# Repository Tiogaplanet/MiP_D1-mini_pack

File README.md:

# MiP Power Up: D1 mini
A [D1 mini](https://wiki.wemos.cc/products:d1:d1_mini) adapter board for [WowWee Labs'](https://github.com/WowWeeLabs/) [MiP](https://wowwee.com/mip) robot.  Similar to the [MiP ProMini Pack](https://github.com/adamgreen/MiP_ProMini-Pack), this board adapts the D1 mini and compatible boards to MiP.  Install the D1 mini in a pair of pin headers and you'll be programming MiP to connect to the Internet in no time.

## Acknowledgment
* As always, a big "thank you" goes out to [adamgreen](https://github.com/adamgreen/).  Without his help I'd still be wondering why my MiP won't talk to an Arduino.  Now, it's talking to the Internet!
* I'd also like to thank [Casey Kuhns](https://github.com/caseykuhns) who while at [SparkFun](https://github.com/sparkfun) developed the original [ProMini Pack](https://github.com/sparkfun/mip_promini-pack) and the [ProtoPack](https://github.com/sparkfun/mip_proto-pack) which provided the foundation for this project.

## OSH Park renderings

## Installation
Please see the [wiki](https://github.com/Tiogaplanet/MPU_D1_mini/wiki) for up-to-date installation instructions.

## Disclaimer
I am a hobbyiest sharing this designed-at-home board with fans of robotics, MiP and the ESP8266 wifi chip.  While I strive to make this board as useful and "right" as it can be, in no way shall I be responsible for any damage that may occur to your MiP or D1 mini either incidently or directly through the use of this board.  You use this board at your own risk.

If you are experienced in robotics or circuit design and spot something that can or should be improved, please review [CONTRIBUTING.md](https://github.com/Tiogaplanet/MPU_D1_mini/blob/master/CONTRIBUTING.md) and submit a pull request.

## License
Shield: [![CC BY-SA 4.0][cc-by-sa-shield]][cc-by-sa]

This work is licensed under a
[Creative Commons Attribution-ShareAlike 4.0 International License][cc-by-sa].

[![CC BY-SA 4.0][cc-by-sa-image]][cc-by-sa]

[cc-by-sa]: http://creativecommons.org/licenses/by-sa/4.0/
[cc-by-sa-image]: https://licensebuttons.net/l/by-sa/4.0/88x31.png
[cc-by-sa-shield]: https://img.shields.io/badge/License-CC%20BY--SA%204.0-lightgrey.svg

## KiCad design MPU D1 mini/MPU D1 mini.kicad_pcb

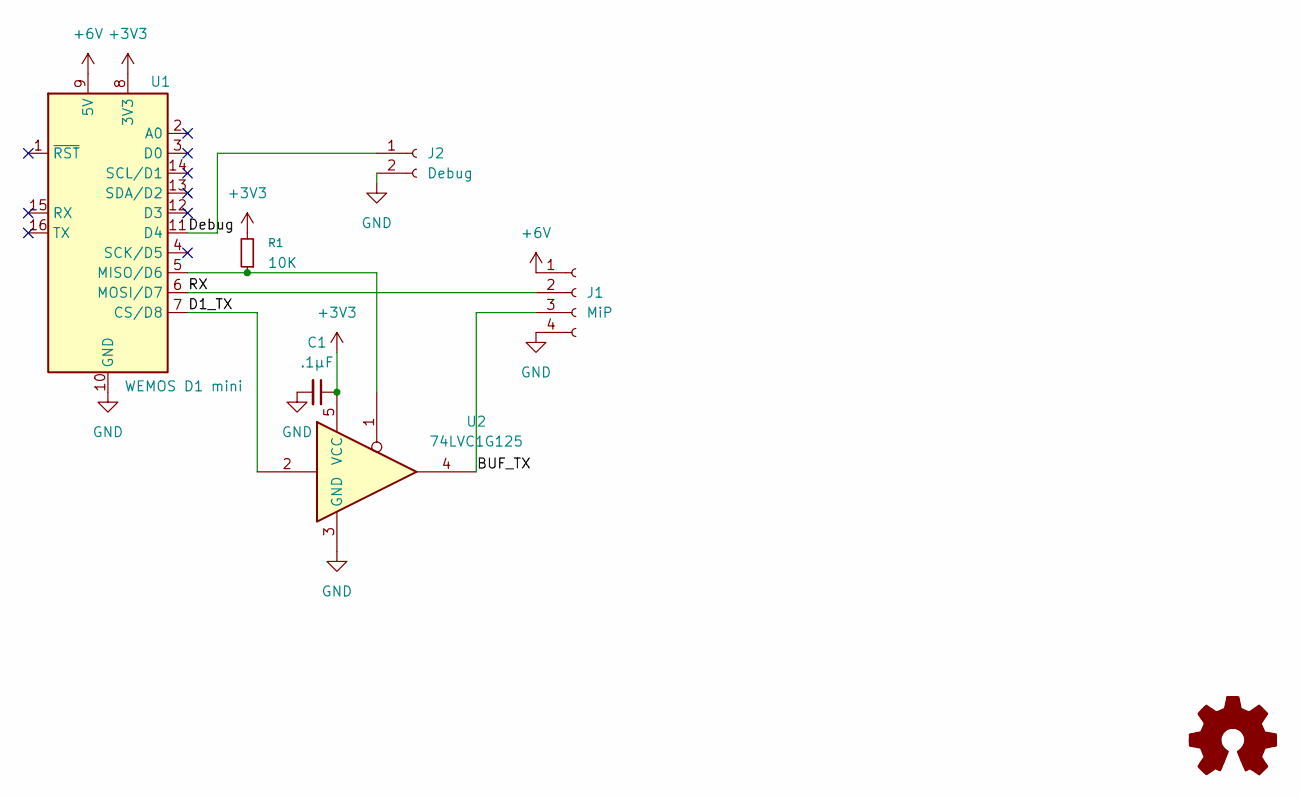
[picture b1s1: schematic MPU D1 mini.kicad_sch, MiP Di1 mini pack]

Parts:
C1: .1μF; C_0805_2012Metric_Pad1.18x1.45mm_HandSolder
J1: MiP; JST_ZH_B4B-ZR_1x04_P1.50mm_Vertical
J2: Debug; PinSocket_1x02_P2.54mm_Horizontal
R1: 10K; R_0805_2012Metric_Pad1.20x1.40mm_HandSolder
U1: WEMOS D1 mini; WEMOS_D1_mini_light
U2: 74LVC1G125; SOT-23-5_HandSoldering

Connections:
+3V3: C1.1, R1.2, U1.8 (3V3), U2.5 (VCC)
+6V: J1.1, U1.9 (5V)
/BUF_TX: J1.3, U2.4
/D1_TX: U1.7 (CS/D8), U2.2
/Debug: J2.1, U1.11 (D4)
/RX: J1.2, U1.6 (MOSI/D7)
GND: C1.2, J1.4, J2.2, U1.10 (GND), U2.3 (GND)
unnamed: R1.1, U1.5 (MISO/D6), U2.1

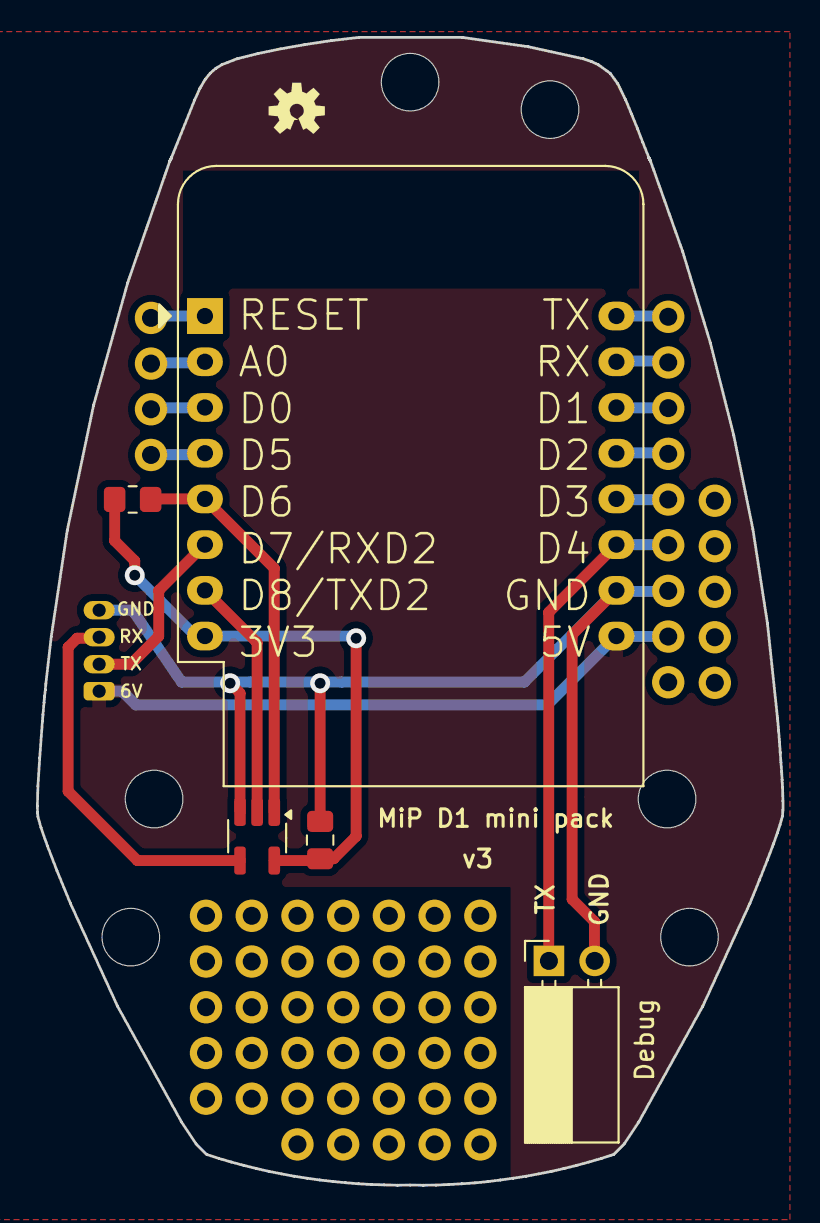
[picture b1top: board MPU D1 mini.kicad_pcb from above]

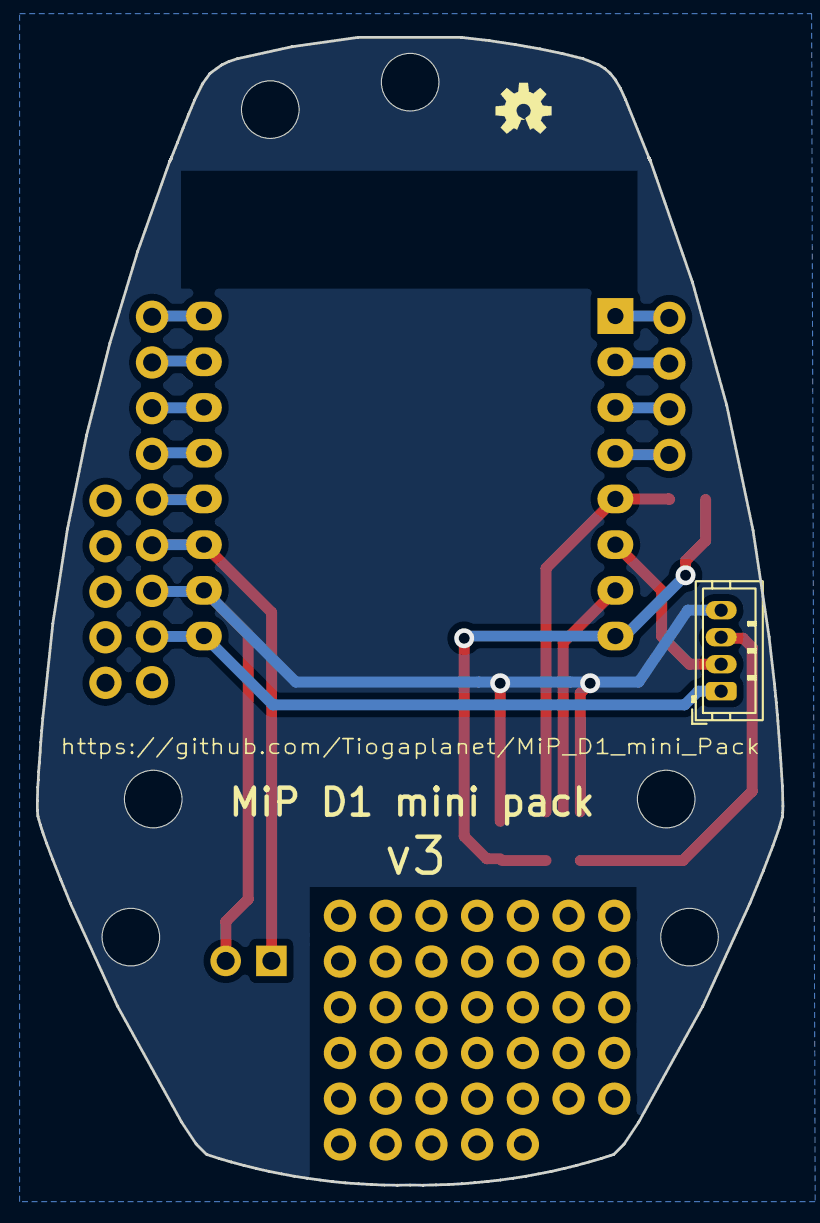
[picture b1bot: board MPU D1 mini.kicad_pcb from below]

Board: 2 copper layers, 41.4 x 63.8 mm, 15 parts (2 on the bottom side), 8 nets.

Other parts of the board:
FRAME1: FRAME-LETTER; CREATIVE_COMMONS
LOGO2, LOGO2#2: OSHW-LOGOS; OSHW-LOGO-S
UNK_HOLE_0: dummyfp0
UNK_HOLE_1: dummyfp1
UNK_HOLE_2: dummyfp2
UNK_HOLE_3: dummyfp3
UNK_HOLE_4: dummyfp4
UNK_HOLE_5: dummyfp5

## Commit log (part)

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2026-06-19 Update README.md
    Changed the image links to point to the images in branch v3
2026-06-19 Update README.md
    Resized the images down to 300px width
2026-06-19 ShareAlike 4.0 license
    Added a section for the SA 4.0 license.
2026-06-20 KiCAD migration
    Moving away from the old standalone Eagle 7.7.0 to use KiCAD instead. And fixing a bug that ooccasionally prevents the D1 mini from booting correctly during the programming and testing cycle.
2026-06-20 Create LICENSE
    Added the whole text of the SA 4.0 license.
2026-06-23 Using tri-state buffer
    Using tri-state buffer, not resistor, to decouple D1 mini from MiP.
2026-06-24 Corrected vias and planes
    Some vias were connected to gthe ground plane,making them useless as a prototyping area.
2026-06-24 Added planes
    No, not flying planes. Added voltage and ground planes.
2026-06-24 Changing case. I don't like title case
2026-06-24 Prototyping area
    Figured out adding prototyping areas.
2026-06-24 Moving files to get rid of duplicated folder name
2026-06-24 Delete MiP D1 mini Pack directory
    Deleted in favor of lower-case p pack directory

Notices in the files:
MPU D1 mini/MPU D1 mini.kicad_sch:
Released under the Creative Commons
https://creativecommons.org/licenses/by-sa/4.0
parts and their libraries:
Released under the Creative Commons Attribution Share-Alike 4.0 License
